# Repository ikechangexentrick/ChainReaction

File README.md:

# ChainReaction
8 step analog sequencer, including two variants of CV and Trigger.

## ChainReaction-Trigger

### [schematic](https://raw.githubusercontent.com/ikechangexentrick/ChainReaction/master/ChainReaction_Trigger_v1.1_schematic.pdf)

## ChainReaction-CV

### [schematic](https://raw.githubusercontent.com/ikechangexentrick/ChainReaction/master/ChainReaction_CV_v1.1_schematic.pdf)

# TBD

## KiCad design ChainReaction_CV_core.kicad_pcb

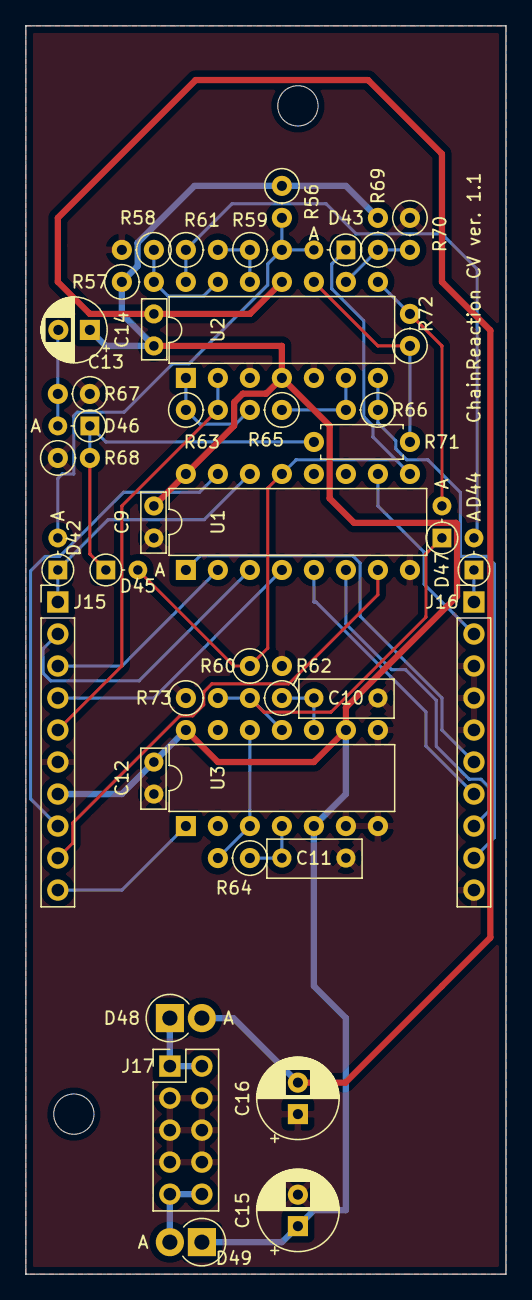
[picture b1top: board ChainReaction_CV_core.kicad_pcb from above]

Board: 2 copper layers, 38.1 x 99.1 mm, 40 parts (0 on the bottom side), 35 nets.

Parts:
C9, C12, C14: 0.1u; C_Axial_L4.8mm_D2.0mm_P2.54mm_Horizontal
C10, C11: 0.1u; C_Axial_L4.8mm_D3.1mm_P5.08mm_Horizontal
C13: 1u; CP_Radial_D5.0mm_P2.50mm
C15, C16: CP; CP_Radial_D6.3mm_P2.50mm
D42, D43, D44, D45, D46, D47: D; D_DO-34_SOD68_P2.54mm_Vertical_AnodeUp
D48, D49: D_Schottky; D_DO-15_P2.54mm_Vertical_AnodeUp
J15: conn_L; PinHeader_1x10_P2.54mm_Vertical
J16: conn_R; PinHeader_1x10_P2.54mm_Vertical
J17: power_bus; PinHeader_2x05_P2.54mm_Vertical
R56, R57, R58, R60, R62, R63, R65, R66, R67, R68, R69, R70, R73: 100k; R_Axial_DIN0207_L6.3mm_D2.5mm_P2.54mm_Vertical
R59, R64: 10k; R_Axial_DIN0207_L6.3mm_D2.5mm_P2.54mm_Vertical
R61, R72: 1M; R_Axial_DIN0207_L6.3mm_D2.5mm_P2.54mm_Vertical
R71: 10k; R_Axial_DIN0207_L6.3mm_D2.5mm_P7.62mm_Horizontal
U1: 4017; DIP-16_W7.62mm
U2: TL074; DIP-14_W7.62mm
U3: 4013; DIP-14_W7.62mm

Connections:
+12V: C9.2, C12.2, C13.1, C14.2, C15.1, D49.1, J15.7, R56.1, R57.1, R69.2, U1.16, U2.4, U3.5, U3.9, U3.14
-12V: C14.1, C16.2, D48.2, U2.11
/CV_Logic/EoC: J15.10, U3.1
/CV_Logic/EoC_in: D47.1, R62.2, R73.2, U3.11
/CV_Logic/Q0: J15.2, U1.3
/CV_Logic/Q1: J15.3, U1.2
/CV_Logic/Q2: J15.4, U1.4
/CV_Logic/Q3: J15.9, U1.7
/CV_Logic/Q4: J16.2, U1.10
/CV_Logic/Q5: J16.6, U1.1
/CV_Logic/Q6: J16.7, U1.5
/CV_Logic/Q7: J16.8, U1.6
/CV_Logic/Q8: D43.1, D45.2, R60.1, U1.9, U1.13
/CV_Logic/clock: D42.1, J15.1, U1.14
/CV_Logic/clock_out: D44.1, J16.1
/CV_Logic/cv: J15.5, R63.2, U2.2
/CV_Logic/cv_out: J16.9, R66.1, U2.7
/CV_Logic/reset: J15.8, U1.15
GND: C9.1, C10.1, C11.1, C12.1, C15.2, C16.1, J15.6, J16.3, J16.4, J16.5, J16.10, J17.3, J17.4, J17.5, J17.6, J17.7, J17.8, R58.2, R60.2, R67.1, R68.1, R70.1, R73.1, U1.8, U2.3, U2.5, U3.6, U3.7, U3.8
unnamed: C10.2, R62.1, U3.10
unnamed: C11.2, R64.1, U3.4
unnamed: C13.2, D46.2, R67.2
unnamed: D42.2, D43.2, R56.2, R59.2
unnamed: D44.2, R61.1, U2.14
unnamed: D45.1, D46.1, R68.2, R71.1
unnamed: D47.2, R72.2, U2.8
unnamed: D48.1, J17.1, J17.2
unnamed: D49.2, J17.9, J17.10
unnamed: R57.2, R58.1, U2.13
unnamed: R59.1, R61.2, U2.12
unnamed: R63.1, R65.2, U2.1
unnamed: R64.2, U3.3, U3.12
unnamed: R65.1, R66.2, U2.6
unnamed: R69.1, R70.2, U2.9
unnamed: R71.2, R72.1, U2.10

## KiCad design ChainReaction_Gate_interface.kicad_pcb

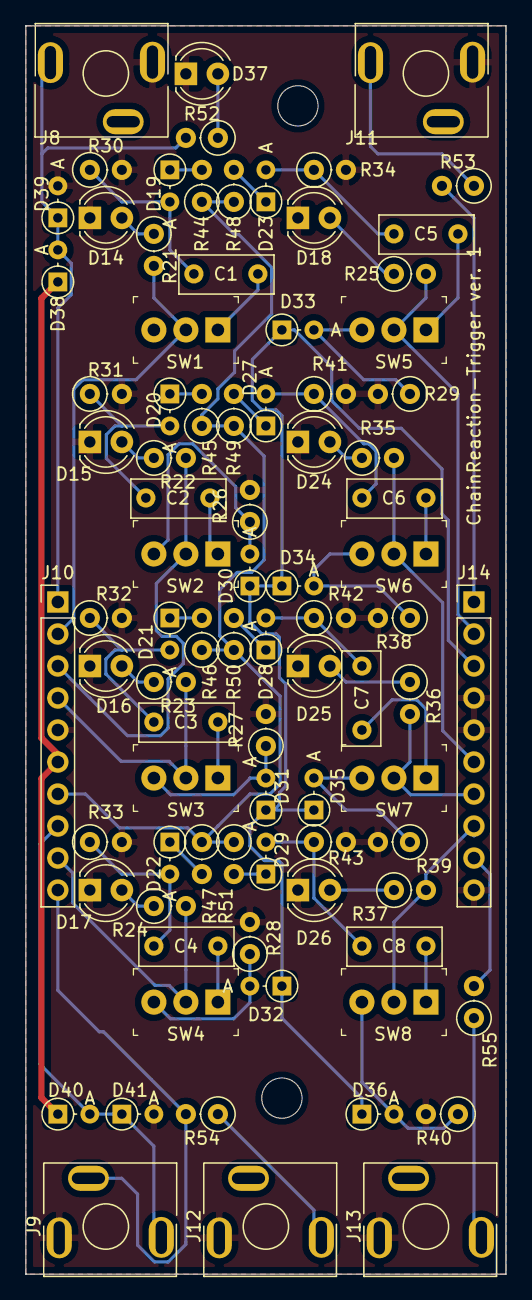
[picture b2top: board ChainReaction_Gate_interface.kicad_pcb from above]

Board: 2 copper layers, 38.1 x 99.1 mm, 102 parts (0 on the bottom side), 60 nets.

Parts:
1, 2, 3, 4, 5, 6, 7, 8: MountingHole_4mm
C1, C2, C3, C4, C5, C6, C7, C8: 0.1u; C_Axial_L4.8mm_D3.1mm_P5.08mm_Horizontal
Clk out: annotation_3.5mm_jack_out
Clock: annotation_3.5mm_jack_in
D14: 1; LED_D4.0mm
D15: 2; LED_D4.0mm
D16: 3; LED_D4.0mm
D17: 4; LED_D4.0mm
D18: 5; LED_D4.0mm
D19, D20, D21, D22, D23, D27, D28, D29, D30, D31, D32, D33, D34, D35, D36, D38, D39, D40, D41: D; D_DO-34_SOD68_P2.54mm_Vertical_AnodeUp
D24: 6; LED_D4.0mm
D25: 7; LED_D4.0mm
D26: 8; LED_D4.0mm
D37: clock; LED_D4.0mm
EoC: annotation_3.5mm_jack_out
J8: clock; MJ-355_3.5mm_mono_jack
J9: reset; MJ-355_3.5mm_mono_jack
J10: conn_L; PinHeader_1x10_P2.54mm_Vertical
J11: clock_out; MJ-355_3.5mm_mono_jack
J12: EoC; MJ-355_3.5mm_mono_jack
J13: trigger_out; MJ-355_3.5mm_mono_jack
J14: conn_R; PinHeader_1x10_P2.54mm_Vertical
On-Off: MountingHole_5mm
On-Off-End: MountingHole_5mm
R21, R22, R23, R24, R25, R35, R36, R37, R52: 10k; R_Axial_DIN0207_L6.3mm_D2.5mm_P2.54mm_Vertical
R26, R27, R28, R29, R30, R31, R32, R33, R34, R38, R39, R40, R41, R42, R43, R44, R45, R46, R47, R48, R49, R50, R51: 100k; R_Axial_DIN0207_L6.3mm_D2.5mm_P2.54mm_Vertical
R53, R54, R55: 1k; R_Axial_DIN0207_L6.3mm_D2.5mm_P2.54mm_Vertical
Reset: annotation_3.5mm_jack_in
SW1: Gate1; Switch_Toggle_on-off-on_akizuki
SW2: Gate2; Switch_Toggle_on-off-on_akizuki
SW3: Gate3; Switch_Toggle_on-off-on_akizuki
SW4: Gate4; Switch_Toggle_on-off-on_akizuki
SW5: Gate5; Switch_Toggle_on-off-on_akizuki
SW6: Gate6; Switch_Toggle_on-off-on_akizuki
SW7: Gate7; Switch_Toggle_on-off-on_akizuki
SW8: Gate8; Switch_Toggle_on-off-on_akizuki
Trigger: annotation_3.5mm_jack_out
clock: MountingHole_4mm

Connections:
+12V: D38.1, D40.1, J10.6
/Trigger_Interface/EoC: J9.TN, J10.10, R54.2
/Trigger_Interface/Q0: J10.2, R21.2, SW1.2
/Trigger_Interface/Q1: J10.3, R22.2, SW2.2
/Trigger_Interface/Q2: J10.4, R23.2, SW3.2
/Trigger_Interface/Q3: J10.9, R24.2, SW4.2
/Trigger_Interface/Q4: J14.2, R25.2, SW5.2
/Trigger_Interface/Q5: J14.6, R35.2, SW6.2
/Trigger_Interface/Q6: J14.7, R36.2, SW7.2
/Trigger_Interface/Q7: J14.8, R37.2, SW8.2
/Trigger_Interface/clock: D38.2, D39.1, J8.T, J10.1, R52.2
/Trigger_Interface/clock_out: J14.1, R53.2
/Trigger_Interface/reset: D40.2, D41.1, J9.T, J10.8
/Trigger_Interface/stop: D30.1, D31.1, D32.1, D33.1, D34.1, D35.1, D36.1, J14.3
/Trigger_Interface/stop2: D30.2, R26.1, SW2.3
/Trigger_Interface/stop3: D31.2, R27.1, SW3.3
/Trigger_Interface/stop4: D32.2, R28.1, SW4.3
/Trigger_Interface/stop5: D33.2, R29.1, SW5.3
/Trigger_Interface/stop6: D34.2, R38.1, SW6.3
/Trigger_Interface/stop7: D35.2, R39.1, SW7.3
/Trigger_Interface/stop8: D36.2, R40.1, SW8.3
/Trigger_Interface/trg: J10.7, R44.1, R45.1, R46.1, R47.1, R48.1, R49.1, R50.1, R51.1
/Trigger_Interface/trg1: D19.1, R44.2
/Trigger_Interface/trg2: D20.1, R45.2
/Trigger_Interface/trg3: D21.1, R46.2
/Trigger_Interface/trg4: D22.1, R47.2
/Trigger_Interface/trg5: D23.1, R48.2
/Trigger_Interface/trg6: D27.1, R49.2
/Trigger_Interface/trg7: D28.1, R50.2
/Trigger_Interface/trg8: D29.1, R51.2
/Trigger_Interface/trigger_out: J14.9, R55.2
GND: D14.1, D15.1, D16.1, D17.1, D18.1, D24.1, D25.1, D26.1, D37.1, D39.2, D41.2, J8.S, J9.S, J10.5, J11.S, J12.S, J13.S, J14.4, J14.5, J14.10, R26.2, R27.2, R28.2, R29.2, R30.2, R31.2, R32.2, R33.2, R34.2, R38.2, R39.2, R40.2, R41.2, R42.2, R43.2
unnamed: C1.1, SW1.1
unnamed: C1.2, D19.2, R30.1
unnamed: C2.1, SW2.1
unnamed: C2.2, D20.2, R31.1
unnamed: C3.1, SW3.1
unnamed: C3.2, D21.2, R32.1
unnamed: C4.1, SW4.1
unnamed: C4.2, D22.2, R33.1
unnamed: C5.1, SW5.1
unnamed: C5.2, D23.2, R34.1
unnamed: C6.1, SW6.1
unnamed: C6.2, D27.2, R41.1
unnamed: C7.1, SW7.1
unnamed: C7.2, D28.2, R42.1
unnamed: C8.1, SW8.1
unnamed: C8.2, D29.2, R43.1
unnamed: D14.2, R21.1
unnamed: D15.2, R22.1
unnamed: D16.2, R23.1
unnamed: D17.2, R24.1
unnamed: D18.2, R25.1
unnamed: D24.2, R35.1
unnamed: D25.2, R36.1
unnamed: D26.2, R37.1
unnamed: D37.2, R52.1
unnamed: J11.T, R53.1
unnamed: J12.T, R54.1
unnamed: J13.T, R55.1

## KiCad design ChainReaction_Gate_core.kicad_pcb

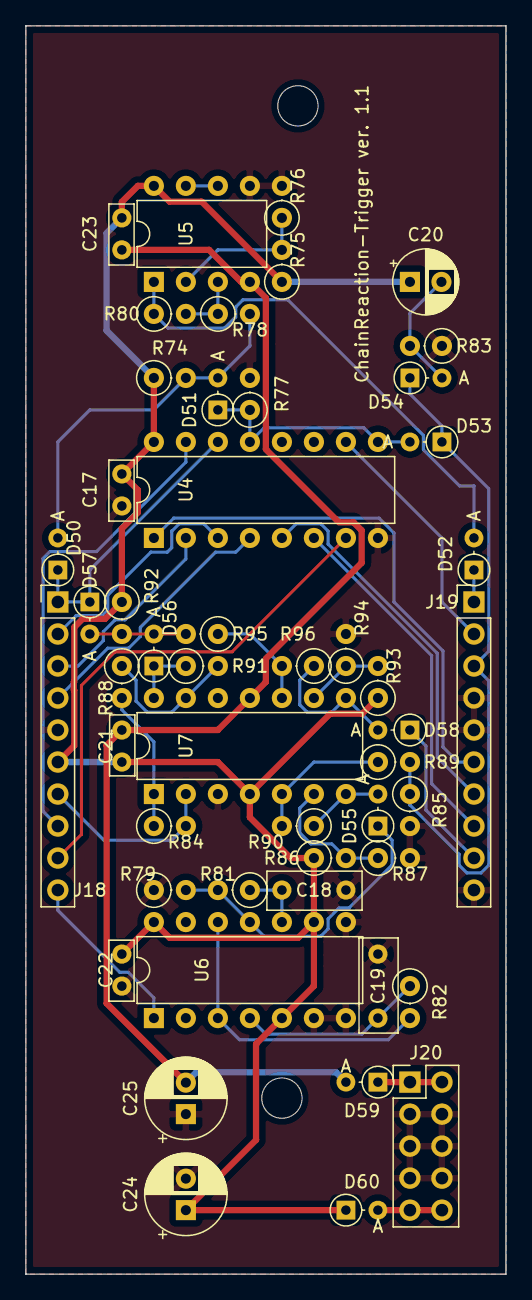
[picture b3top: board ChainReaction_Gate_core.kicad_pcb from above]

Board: 2 copper layers, 38.1 x 99.1 mm, 50 parts (0 on the bottom side), 41 nets.

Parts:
C17, C21, C22, C23: 0.1u; C_Axial_L4.8mm_D2.0mm_P2.54mm_Horizontal
C18, C19: 0.1u; C_Axial_L4.8mm_D3.1mm_P5.08mm_Horizontal
C20: 1u; CP_Radial_D5.0mm_P2.50mm
C24, C25: CP; CP_Radial_D6.3mm_P2.50mm
D50, D51, D52, D53, D54, D55, D56, D57, D58: D; D_DO-34_SOD68_P2.54mm_Vertical_AnodeUp
D59, D60: D_Schottky; D_DO-34_SOD68_P2.54mm_Vertical_AnodeUp
J18: conn_L; PinHeader_1x10_P2.54mm_Vertical
J19: conn_R; PinHeader_1x10_P2.54mm_Vertical
J20: power_bus; PinHeader_2x05_P2.54mm_Vertical
R74, R75, R76, R77, R81, R82, R84, R85, R86, R87, R88, R91, R92, R93, R94: 100k; R_Axial_DIN0207_L6.3mm_D2.5mm_P2.54mm_Vertical
R78, R79, R89, R95: 10k; R_Axial_DIN0207_L6.3mm_D2.5mm_P2.54mm_Vertical
R80, R83, R90, R96: 1M; R_Axial_DIN0207_L6.3mm_D2.5mm_P2.54mm_Vertical
U4: 4017; DIP-16_W7.62mm
U5: TL072; DIP-8_W7.62mm
U6: 4013; DIP-14_W7.62mm
U7: TL074; DIP-14_W7.62mm

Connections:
+12V: C17.2, C20.1, C21.2, C22.2, C23.2, C24.1, D60.1, J18.6, R74.1, R75.1, R86.1, R92.1, R93.1, U4.16, U5.8, U6.5, U6.9, U6.14, U7.4
-12V: C21.1, C23.1, C25.2, D59.2, U5.4, U7.11
/Trigger_Logic/EoC: J18.10, U6.1
/Trigger_Logic/EoC_in: D55.1, R79.2, R81.2, U6.11
/Trigger_Logic/Q0: J18.2, U4.3
/Trigger_Logic/Q1: J18.3, U4.2
/Trigger_Logic/Q2: J18.4, U4.4
/Trigger_Logic/Q3: J18.9, U4.7
/Trigger_Logic/Q4: J19.2, U4.10
/Trigger_Logic/Q5: J19.6, U4.1
/Trigger_Logic/Q6: J19.7, U4.5
/Trigger_Logic/Q7: J19.8, U4.6
/Trigger_Logic/Q8: D51.1, D53.2, R77.1, U4.9, U4.13
/Trigger_Logic/clock: D50.1, D57.1, J18.1, U4.14
/Trigger_Logic/clock_out: D52.1, J19.1
/Trigger_Logic/reset: J18.8, U4.15
/Trigger_Logic/stop: D53.1, D54.1, J19.3, R85.1, R89.2
/Trigger_Logic/trg: J18.7, R84.2, U7.2
/Trigger_Logic/trigger_out: D58.1, J19.9
GND: C17.1, C18.1, C19.1, C22.1, C24.2, C25.1, J18.5, J19.4, J19.5, J19.10, J20.3, J20.4, J20.5, J20.6, J20.7, J20.8, R76.2, R77.2, R79.1, R83.1, R85.2, R87.2, R94.2, U4.8, U5.5, U6.6, U6.7, U6.8, U7.3, U7.12
unnamed: C18.2, R81.1, U6.10
unnamed: C19.2, R82.1, U6.4
unnamed: C20.2, D54.2, R83.2
unnamed: D50.2, D51.2, R74.2, R78.2
unnamed: D52.2, R80.1, U5.1
unnamed: D55.2, R90.1, U7.7
unnamed: D56.1, R91.1, U7.14
unnamed: D56.2, D57.2, R92.2, R95.2
unnamed: D58.2, R96.1, U7.8
unnamed: D59.1, J20.1, J20.2
unnamed: D60.2, J20.9, J20.10
unnamed: R75.2, R76.1, U5.2
unnamed: R78.1, R80.2, U5.3
unnamed: R82.2, U6.3, U6.12
unnamed: R84.1, R88.2, U7.1
unnamed: R86.2, R87.1, U7.6
unnamed: R88.1, R91.2, U7.13
unnamed: R89.1, R90.2, U7.5
unnamed: R93.2, R94.1, U7.9
unnamed: R95.1, R96.2, U7.10
unnamed: U5.6, U5.7

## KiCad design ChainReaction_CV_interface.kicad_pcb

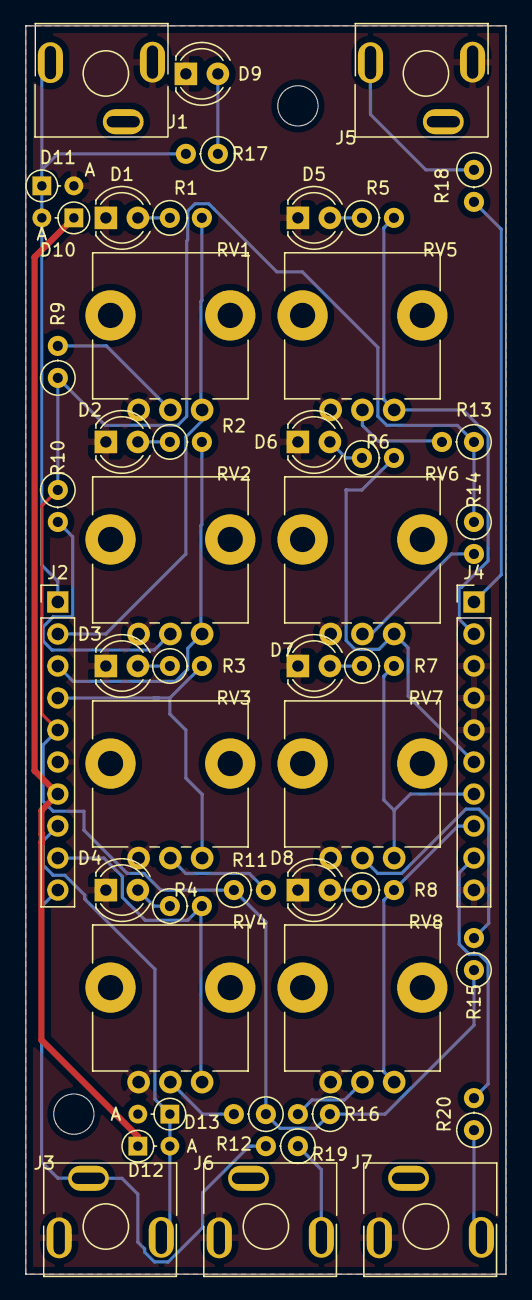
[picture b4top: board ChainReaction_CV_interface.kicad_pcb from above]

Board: 2 copper layers, 38.1 x 99.1 mm, 61 parts (0 on the bottom side), 36 nets.

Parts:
1, 2, 3, 4, 5, 6, 7, 8: MountingHole_4mm
CV: annotation_3.5mm_jack_out
Clk out: annotation_3.5mm_jack_out
Clock: annotation_3.5mm_jack_in
D1, D2, D3, D4, D5, D6, D7, D8, D9: LED; LED_D4.0mm
D10, D11, D12, D13: D; D_DO-34_SOD68_P2.54mm_Vertical_AnodeUp
EoC: annotation_3.5mm_jack_out
J1: clock; MJ-355_3.5mm_mono_jack
J2: conn_L; PinHeader_1x10_P2.54mm_Vertical
J3: reset; MJ-355_3.5mm_mono_jack
J4: conn_R; PinHeader_1x10_P2.54mm_Vertical
J5: clock_out; MJ-355_3.5mm_mono_jack
J6: EoC; MJ-355_3.5mm_mono_jack
J7: cv_out; MJ-355_3.5mm_mono_jack
R1, R2, R3, R4, R5, R6, R7, R8, R17: 10k; R_Axial_DIN0207_L6.3mm_D2.5mm_P2.54mm_Vertical
R9, R10, R11, R12, R13, R14, R15, R16: 100k; R_Axial_DIN0207_L6.3mm_D2.5mm_P2.54mm_Vertical
R18, R19, R20: 1k; R_Axial_DIN0207_L6.3mm_D2.5mm_P2.54mm_Vertical
RV1, RV2, RV3, RV4, RV5, RV6, RV7, RV8: 10kB; Potentiometer_Alps_RK09L_Single_Vertical
Reset: annotation_3.5mm_jack_in

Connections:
+12V: D10.1, D12.1, J2.7
/CV_interface/EoC: J2.10, J3.TN, R19.2
/CV_interface/Q0: J2.2, R1.2, RV1.3
/CV_interface/Q1: J2.3, R2.2, RV2.3
/CV_interface/Q2: J2.4, R3.2, RV3.3
/CV_interface/Q3: J2.9, R4.2, RV4.3
/CV_interface/Q4: J4.2, R5.2, RV5.3
/CV_interface/Q5: J4.6, R6.2, RV6.3
/CV_interface/Q6: J4.7, R7.2, RV7.3
/CV_interface/Q7: J4.8, R8.2, RV8.3
/CV_interface/clock: D10.2, D11.1, J1.T, J2.1, R17.2
/CV_interface/clock_out: J4.1, R18.2
/CV_interface/cv: J2.5, R9.1, R10.1, R11.1, R12.1, R13.1, R14.1, R15.1, R16.1
/CV_interface/cv1: R9.2, RV1.2
/CV_interface/cv2: R10.2, RV2.2
/CV_interface/cv3: R11.2, RV3.2
/CV_interface/cv4: R12.2, RV4.2
/CV_interface/cv5: R13.2, RV5.2
/CV_interface/cv6: R14.2, RV6.2
/CV_interface/cv7: R15.2, RV7.2
/CV_interface/cv8: R16.2, RV8.2
/CV_interface/cv_out: J4.9, R20.2
/CV_interface/reset: D12.2, D13.1, J2.8, J3.T
GND: D1.1, D2.1, D3.1, D4.1, D5.1, D6.1, D7.1, D8.1, D9.1, D11.2, D13.2, J1.S, J2.6, J3.S, J4.3, J4.4, J4.5, J4.10, J5.S, J6.S, J7.S, RV1.1, RV2.1, RV3.1, RV4.1, RV5.1, RV6.1, RV7.1, RV8.1
unnamed: D1.2, R1.1
unnamed: D2.2, R2.1
unnamed: D3.2, R3.1
unnamed: D4.2, R4.1
unnamed: D5.2, R5.1
unnamed: D6.2, R6.1
unnamed: D7.2, R7.1
unnamed: D8.2, R8.1
unnamed: D9.2, R17.1
unnamed: J5.T, R18.1
unnamed: J6.T, R19.1
unnamed: J7.T, R20.1

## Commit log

2022-09-12 8 step analog sequencer "ChainReaction". There are two variants included; CV and Trigger.
2022-09-24 Fixed problems: - added power-on reset function - added 100ks to discharge caps with FFs(4013) - only for the CV; adjusted the parameter (100k -> 10k) of a resistor with a FF
2022-09-26 adjusted some silks.
2022-09-30 Added schematics.
2022-09-30 branch for images on README.md
